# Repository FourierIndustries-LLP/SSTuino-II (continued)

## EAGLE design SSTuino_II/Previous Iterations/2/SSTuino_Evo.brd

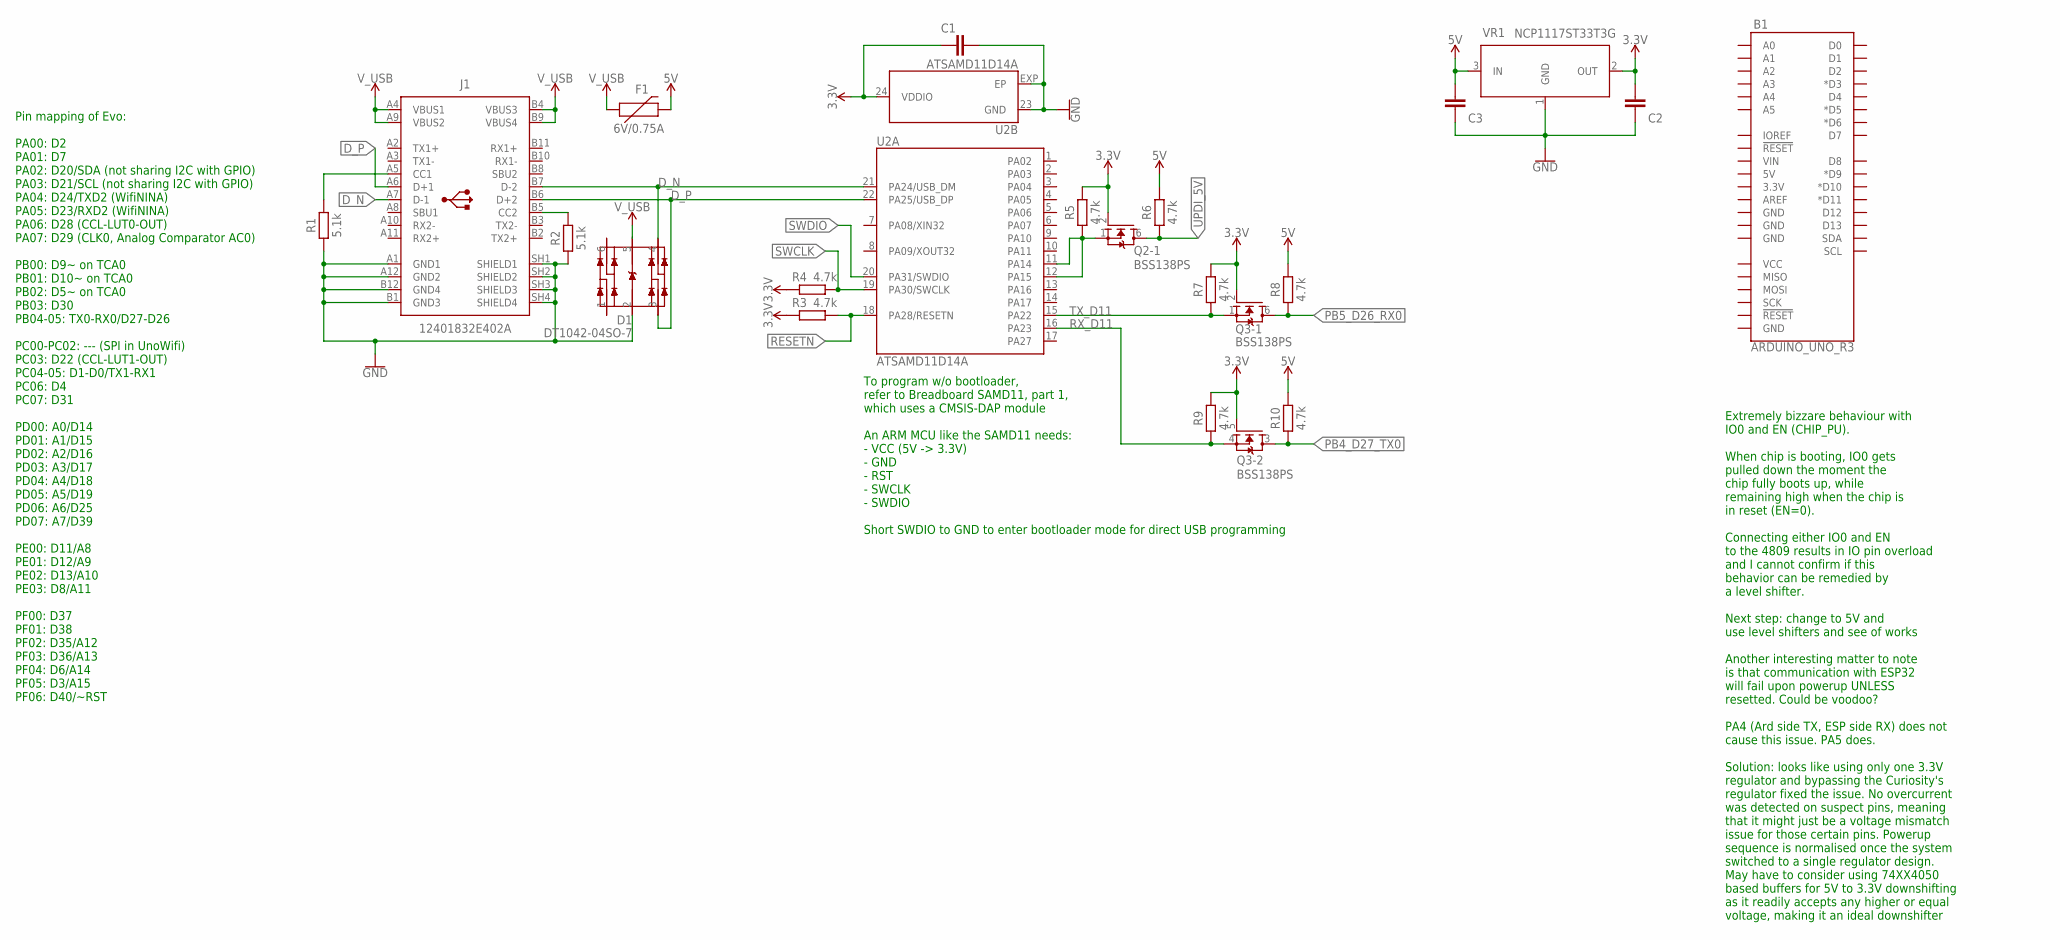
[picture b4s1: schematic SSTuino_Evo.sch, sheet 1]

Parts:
B1: ARDUINO_UNO_R3; ARDUINO_R3
C1: 100n; CAPC1005X60
C2, C3: 10uF; CAPC1608X85
D1: DT1042-04SO-7; SOT95P285X140-6N
F1: 6V/0.75A; 1206
J1: 12401832E402A
Q2, Q3: BSS138PS; ARDUINO-TRANSISTORS_SOT363
R1, R2: 5.1k; RESC1005X40
R3, R4, R5, R6, R7, R8, R9, R10: 4.7k; RESC1005X40
U2: ATSAMD11D14A; ARDUINO-UCS&SOCS_HVQFN24
VR1: NCP1117ST33T3G; SOT230P700X170-4

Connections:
3.3V: C1.1, C2.1, Q2.2 (G), Q3.2 (G), Q3.5 (G), R3.2, R4.2, R5.2, R7.2, R9.2, U2.24 (VDDIO), VR1.2 (OUT); also elsewhere on the board
5V: C3.1, F1.2, R6.2, R8.2, R10.2, VR1.3 (IN); also elsewhere on the board
CC1: J1.A5 (CC1), R1.2
CC2: J1.B5 (CC2), R2.2
D_N: D1.4 (IO3), J1.A7 (D-1), J1.B7 (D-2), U2.21 (PA24/USB_DM)
D_P: D1.3 (IO2), J1.A6 (D+1), J1.B6 (D+2), U2.22 (PA25/USB_DP)
GND: C1.2, C2.2, C3.2, D1.2 (VSS), J1.A1 (GND1), J1.A12 (GND2), J1.B1 (GND3), J1.B12 (GND4), J1.SH1 (SHIELD1), J1.SH2 (SHIELD2), J1.SH3 (SHIELD3), J1.SH4 (SHIELD4), R1.1, R2.1, U2.23 (GND), U2.EXP (EP), VR1.1 (GND); also elsewhere on the board
PB4_D27_TX0: Q3.3 (D), R10.1; also elsewhere on the board
PB5_D26_RX0: Q3.6 (D), R8.1; also elsewhere on the board
RESETN: R3.1, U2.18 (PA28/RESETN)
RX_D11: Q3.4 (S), R9.1, U2.16 (PA23)
SWCLK: R4.1, U2.19 (PA30/SWCLK)
SWDIO: U2.20 (PA31/SWDIO)
TX_D11: Q3.1 (S), R7.1, U2.15 (PA22)
UPDI_3V3: Q2.1 (S), R5.1, U2.11 (PA14), U2.12 (PA15)
UPDI_5V: Q2.6 (D), R6.1
V_USB: D1.5 (VCC), F1.1, J1.A4 (VBUS1), J1.A9 (VBUS2), J1.B4 (VBUS3), J1.B9 (VBUS4)

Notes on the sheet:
Pin mapping of Evo: PA00: D2 PA01: D7 PA02: D20/SDA (not sharing I2C with GPIO) PA03: D21/SCL (not sharing I2C with GPIO) PA04: D24/TXD2 (WifiNINA) PA05: D23/RXD2 (WifiNINA) PA06: D28 (CCL-LUT0-OUT) PA07: D29 (CLK0, Analog Comparator AC0) PB00: D9~ on TCA0 PB01: D10~ on TCA0 PB02: D5~ on TCA0 PB03: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
To program w/o bootloader, refer to Breadboard SAMD11, part 1, which uses a CMSIS-DAP module An ARM MCU like the SAMD11 needs: - VCC (5V -> 3.3V) - GND - RST - SWCLK - SWDIO Short SWDIO to GND to enter bootloader mode for direct USB programming
Extremely bizzare behaviour with IO0 and EN (CHIP_PU). When chip is booting, IO0 gets pulled down the moment the chip fully boots up, while remaining high when the chip is in reset (EN=0). Connecting either IO0 and EN to the 4809 results in IO pin overload and I cannot confirm if this behavior can 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

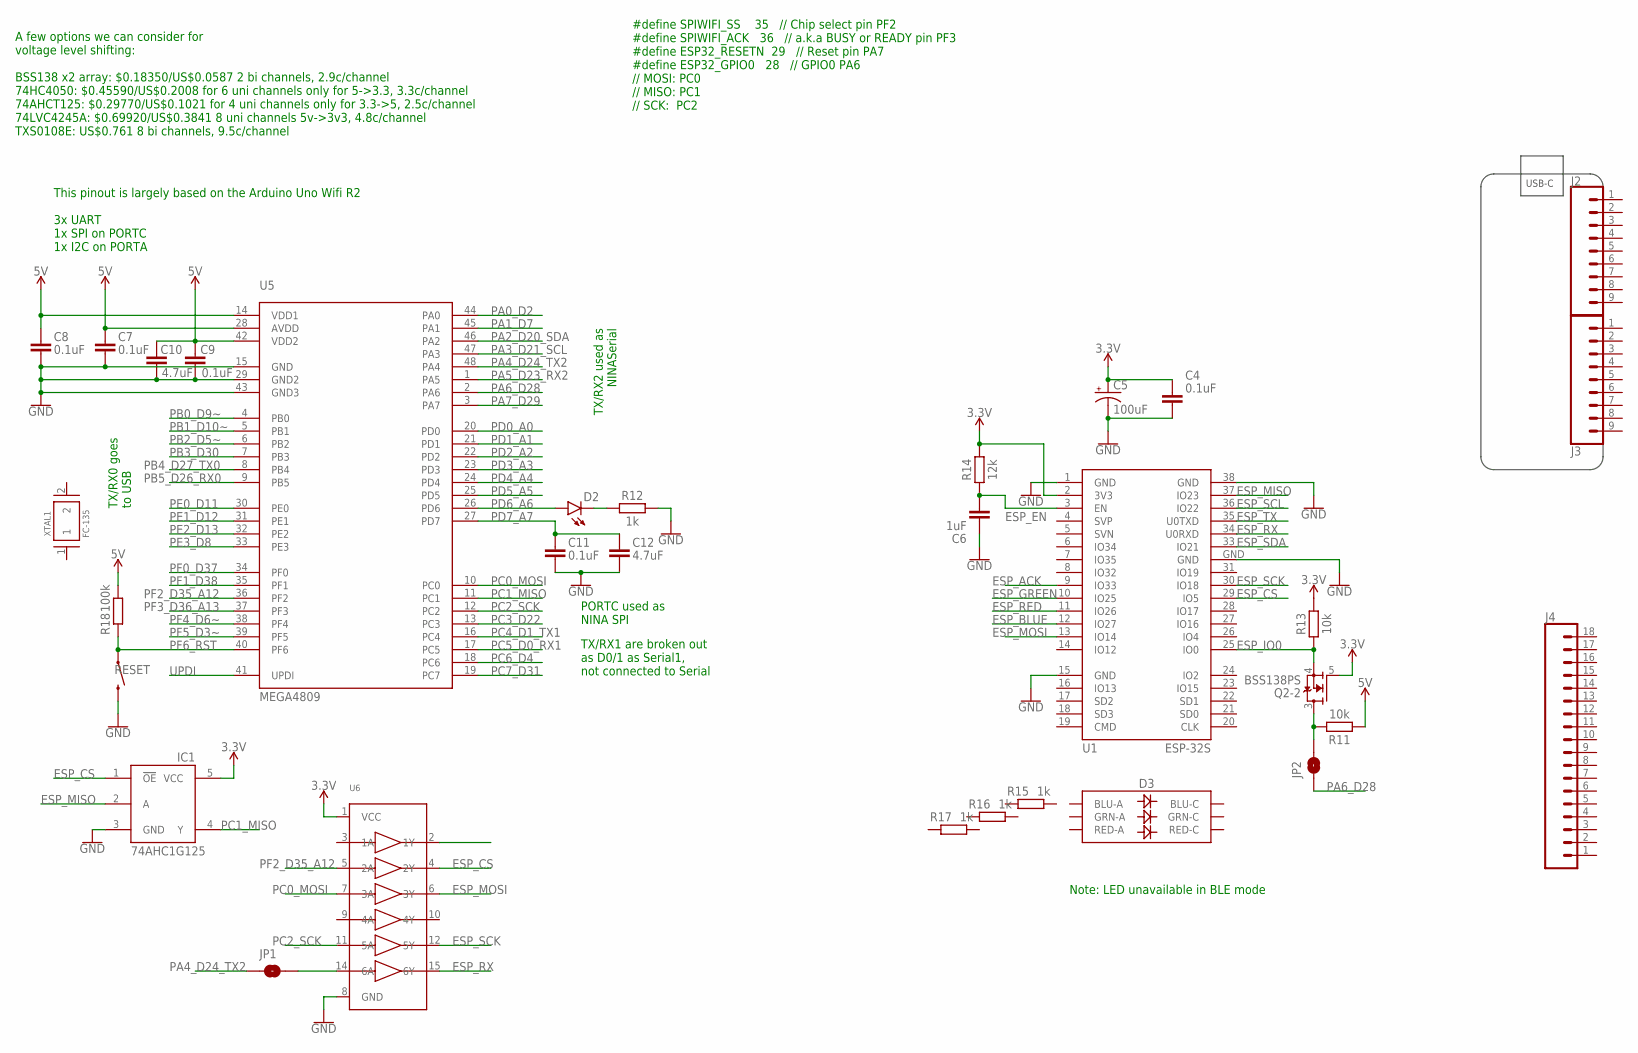
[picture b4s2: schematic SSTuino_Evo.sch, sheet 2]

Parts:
C4, C7, C8, C9, C11: 0.1uF; CAPC1005X60
C5: 100uF; CAPMP3216X180N
C6: 1uF; CAPC1005X60
C10, C12: 4.7uF; CAPC1005X60
D2: LED0603; LED-0603
D3: LED-RGBNO_IC; LED-TRICOLOR-5050
IC1: 74AHC1G125; SOT23-5L
J2, J3: CONN_09NO_SILK; 1X09_NO_SILK
J4: CONN_18; 1X18
JP1, JP2: JUMPER-SMT_2_NO_SILK; SMT-JUMPER_2_NO_SILK
Q2: BSS138PS; ARDUINO-TRANSISTORS_SOT363
R11, R13: 10k; RESC1005X40
R12, R15, R16, R17: 1k; RESC1005X40
R14: 12k; RESC1005X40
R18: 100k; RESC1005X40
RESET: MOMENTARY-SWITCH-SPST-SMD-4.6X2.8MM; TACTILE_SWITCH_SMD_4.6X2.8MM
U1: ESP-32S
U5: MEGA4809; TQFP48
U6: 74HC4050DTSSOP; TSSOP16
XTAL1: FC-135; XTAL330X1051X90N

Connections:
3.3V: C4.1, C5.1 (+), IC1.5 (VCC), Q2.5 (G), R13.2, R14.2, U1.2 (3V3), U6.1 (VCC); also elsewhere on the board
5V: C7.1, C8.1, C9.1, C10.1, R11.1, R18.2, U5.14 (VDD1), U5.28 (AVDD), U5.42 (VDD2); also elsewhere on the board
ESP_ACK: U1.9 (IO33)
ESP_BLUE: U1.12 (IO27)
ESP_CS: IC1.1 (!OE), U1.29 (IO5), U6.4 (2Y)
ESP_EN: C6.2, R14.1, U1.3 (EN)
ESP_GREEN: U1.10 (IO25)
ESP_IO0: Q2.4 (S), R13.1, U1.25 (IO0)
ESP_MISO: IC1.2 (A), U1.37 (IO23)
ESP_MOSI: U1.13 (IO14), U6.6 (3Y)
ESP_RED: U1.11 (IO26)
ESP_RX: U1.34 (U0RXD), U6.15 (6Y)
ESP_SCK: U1.30 (IO18), U6.12 (5Y)
ESP_SCL: U1.36 (IO22)
ESP_SDA: U1.33 (IO21)
ESP_TX: U1.35 (U0TXD)
GND: C4.2, C5.2 (-), C6.1, C7.2, C8.2, C9.2, C10.2, C11.2, C12.2, IC1.3 (GND), R12.2, RESET.3 (2), RESET.4 (2), U1.1 (GND), U1.15 (GND), U1.38 (GND), U1.GND, U5.15 (GND), U5.29 (GND2), U5.43 (GND3), U6.8 (GND); also elsewhere on the board
unnamed: JP2.2, Q2.3 (D), R11.2
unnamed: D2.C, R12.1
unnamed: JP1.2, U6.14 (6A)
PA0_D2: U5.44 (PA0)
PA1_D7: U5.45 (PA1)
PA2_D20_SDA: U5.46 (PA2)
PA3_D21_SCL: U5.47 (PA3)
PA4_D24_TX2: JP1.1, U5.48 (PA4)
PA5_D23_RX2: U5.1 (PA5)
PA6_D28: JP2.1, U5.2 (PA6)
PA7_D29: U5.3 (PA7)
PB0_D9~: U5.4 (PB0)
PB1_D10~: U5.5 (PB1)
PB2_D5~: U5.6 (PB2)
PB3_D30: U5.7 (PB3)
PB4_D27_TX0: U5.8 (PB4); also elsewhere on the board
PB5_D26_RX0: U5.9 (PB5); also elsewhere on the board
PC0_MOSI: U5.10 (PC0), U6.7 (3A)
PC1_MISO: IC1.4 (Y), U5.11 (PC1)
PC2_SCK: U5.12 (PC2), U6.11 (5A)
PC3_D22: U5.13 (PC3)
PC4_D1_TX1: U5.16 (PC4)
PC5_D0_RX1: U5.17 (PC5)
PC6_D4: U5.18 (PC6)
PC7_D31: U5.19 (PC7)
PD0_A0: U5.20 (PD0)
PD1_A1: U5.21 (PD1)
PD2_A2: U5.22 (PD2)
PD3_A3: U5.23 (PD3)
PD4_A4: U5.24 (PD4)
PD5_A5: U5.25 (PD5)
PD6_A6: D2.A, U5.26 (PD6)
PD7_A7: C11.1, C12.1, U5.27 (PD7)
PE0_D11: U5.30 (PE0)
PE1_D12: U5.31 (PE1)
PE2_D13: U5.32 (PE2)
PE3_D8: U5.33 (PE3)
PF0_D37: U5.34 (PF0)
PF1_D38: U5.35 (PF1)
PF2_D35_A12: U5.36 (PF2), U6.5 (2A)
PF3_D36_A13: U5.37 (PF3)
PF4_D6~: U5.38 (PF4)
PF5_D3~: U5.39 (PF5)
PF6_RST: R18.1, RESET.1, RESET.2 (1), U5.40 (PF6)
UPDI: U5.41 (UPDI)

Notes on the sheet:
A few options we can consider for voltage level shifting: BSS138 x2 array: $0.18350/US$0.0587 2 bi channels, 2.9c/channel 74HC4050: $0.45590/US$0.2008 for 6 uni channels only for 5->3.3, 3.3c/channel 74AHCT125: $0.29770/US$0.1021 for 4 uni channels only for 3.3->5, 2.5c/channel 74LVC4245A: $0.69920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
This pinout is largely based on the Arduino Uno Wifi R2 3x UART 1x SPI on PORTC 1x I2C on PORTA
TX/RX2 used as NINASerial
PORTC used as NINA SPI
TX/RX1 are broken out as D0/1 as Serial1, not connected to Serial
TX/RX0 goes to USB
#define SPIWIFI_SS 35 // Chip select pin PF2 #define SPIWIFI_ACK 36 // a.k.a BUSY or READY pin PF3 #define ESP32_RESETN 29 // Reset pin PA7 #define ESP32_GPIO0 28 // GPIO0 PA6 // MOSI: PC0 // MISO: PC1 // SCK: PC2
Note: LED unavailable in BLE mode
USB-C

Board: 2 copper layers, 51 parts (0 on the bottom side), 35 nets, no tracks yet.

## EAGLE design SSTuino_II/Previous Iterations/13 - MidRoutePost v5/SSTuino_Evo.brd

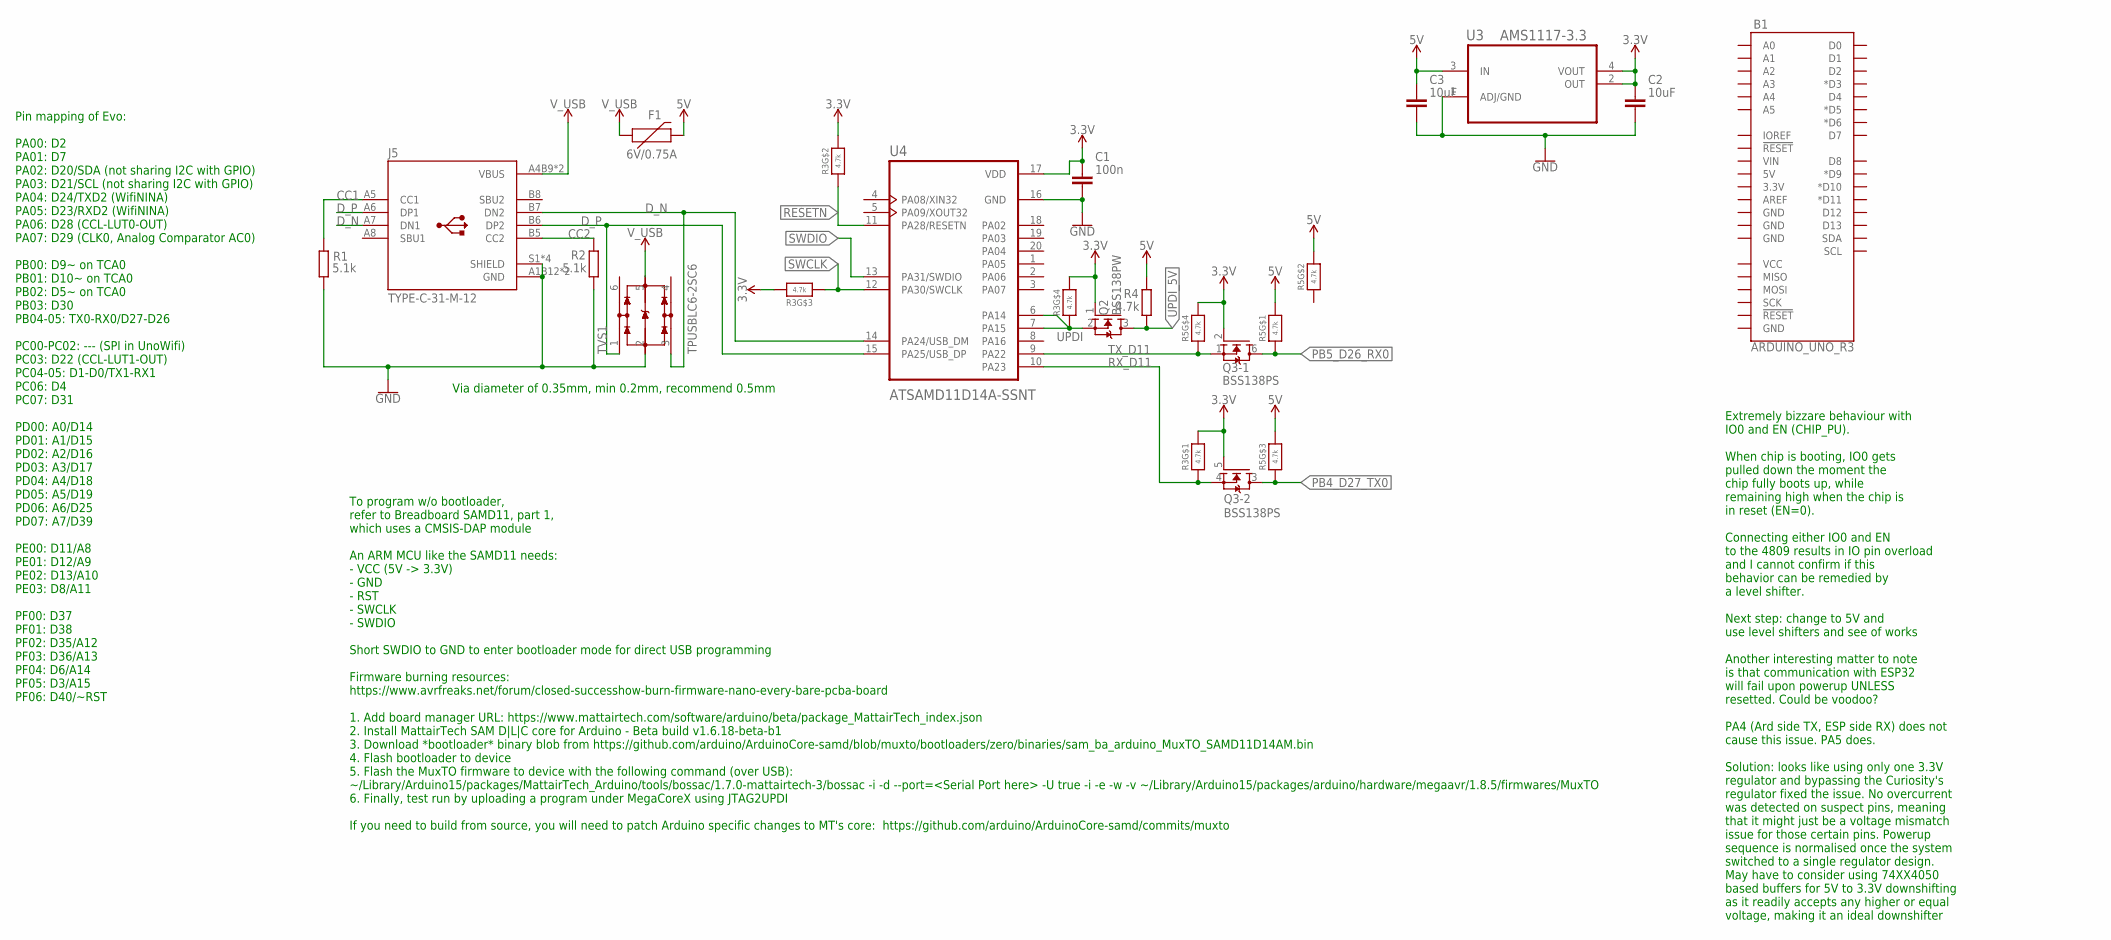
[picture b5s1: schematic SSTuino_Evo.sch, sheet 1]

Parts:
B1: ARDUINO_UNO_R3; ARDUINO_R3
C1: 100n; CAPC1005X60
C2, C3: 10uF; CAPC1608X85
F1: 6V/0.75A; 1206; LCSC_PART C99563
J5: TYPE-C-31-M-12; HRO_TYPE-C-31-M-12; LCSC_PART C165948
Q2: BSS138PW; SOT65P210X110-3N
Q3: BSS138PS; ARDUINO-TRANSISTORS_SOT363; LCSC_PART C193381
R1, R2: 5.1k; RESC1005X40
R3, R5: 4.7k; RESPACK_4X0402; LCSC_PART C1980
R4: 4.7k; RESC1005X40
TVS1: TPUSBLC6-2SC6; SOT95P280X110-6N; LCSC_PART C558442
U3: AMS1117-3.3; SOT230P696X180-4N; LCSC_PART C6186
U4: ATSAMD11D14A-SSNT; SOIC127P1030X265-20N; LCSC_PART C2053599

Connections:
3.3V: C1.1, C2.1, Q2.1 (G), Q3.2 (G), Q3.5 (G), R3.5 (2), R3.6 (2), R3.7 (2), R3.8 (2), R5.5 (2), U3.2 (OUT), U3.4 (VOUT), U4.17 (VDD); also elsewhere on the board
5V: C3.1, F1.2, R4.2, R5.6 (2), R5.7 (2), R5.8 (2), U3.3 (IN); also elsewhere on the board
CC1: J5.A5 (CC1), R1.1
CC2: J5.B5 (CC2), R2.2
D_N: J5.A7 (DN1), J5.B7 (DN2), TVS1.3 (IO2), U4.14 (PA24/USB_DM)
D_P: J5.A6 (DP1), J5.B6 (DP2), TVS1.1 (IO1), U4.15 (PA25/USB_DP)
GND: C1.2, C2.2, C3.2, J5.A1B12 (GND), J5.B1A12 (GND), J5.S1 (SHIELD), J5.S2 (SHIELD), J5.S3 (SHIELD), J5.S4 (SHIELD), R1.2, R2.1, TVS1.2 (VSS), U3.1 (ADJ/GND), U4.16 (GND); also elsewhere on the board
PB4_D27_TX0: Q3.3 (D), R5.3 (1); also elsewhere on the board
PB5_D26_RX0: Q3.6 (D), R5.1; also elsewhere on the board
RESETN: R3.2 (1), U4.11 (PA28/RESETN); also elsewhere on the board
RX_D11: Q3.4 (S), R3.1, U4.10 (PA23)
SWCLK: R3.3 (1), U4.12 (PA30/SWCLK); also elsewhere on the board
SWDIO: U4.13 (PA31/SWDIO); also elsewhere on the board
TX_D11: Q3.1 (S), R5.4 (1), U4.9 (PA22)
UPDI: Q2.2 (S), R3.4 (1), U4.6 (PA14), U4.7 (PA15)
UPDI_5V: Q2.3 (D), R4.1; also elsewhere on the board
V_USB: F1.1, J5.A4B9 (VBUS), J5.B4A9 (VBUS), TVS1.5 (VCC)

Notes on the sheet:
Pin mapping of Evo: PA00: D2 PA01: D7 PA02: D20/SDA (not sharing I2C with GPIO) PA03: D21/SCL (not sharing I2C with GPIO) PA04: D24/TXD2 (WifiNINA) PA05: D23/RXD2 (WifiNINA) PA06: D28 (CCL-LUT0-OUT) PA07: D29 (CLK0, Analog Comparator AC0) PB00: D9~ on TCA0 PB01: D10~ on TCA0 PB02: D5~ on TCA0 PB03: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
To program w/o bootloader, refer to Breadboard SAMD11, part 1, which uses a CMSIS-DAP module An ARM MCU like the SAMD11 needs: - VCC (5V -> 3.3V) - GND - RST - SWCLK - SWDIO Short SWDIO to GND to enter bootloader mode for direct USB programming Firmware burning resources: https://www.avrfreaks.net/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
Extremely bizzare behaviour with IO0 and EN (CHIP_PU). When chip is booting, IO0 gets pulled down the moment the chip fully boots up, while remaining high when the chip is in reset (EN=0). Connecting either IO0 and EN to the 4809 results in IO pin overload and I cannot confirm if this behavior can 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
Via diameter of 0.35mm, min 0.2mm, recommend 0.5mm

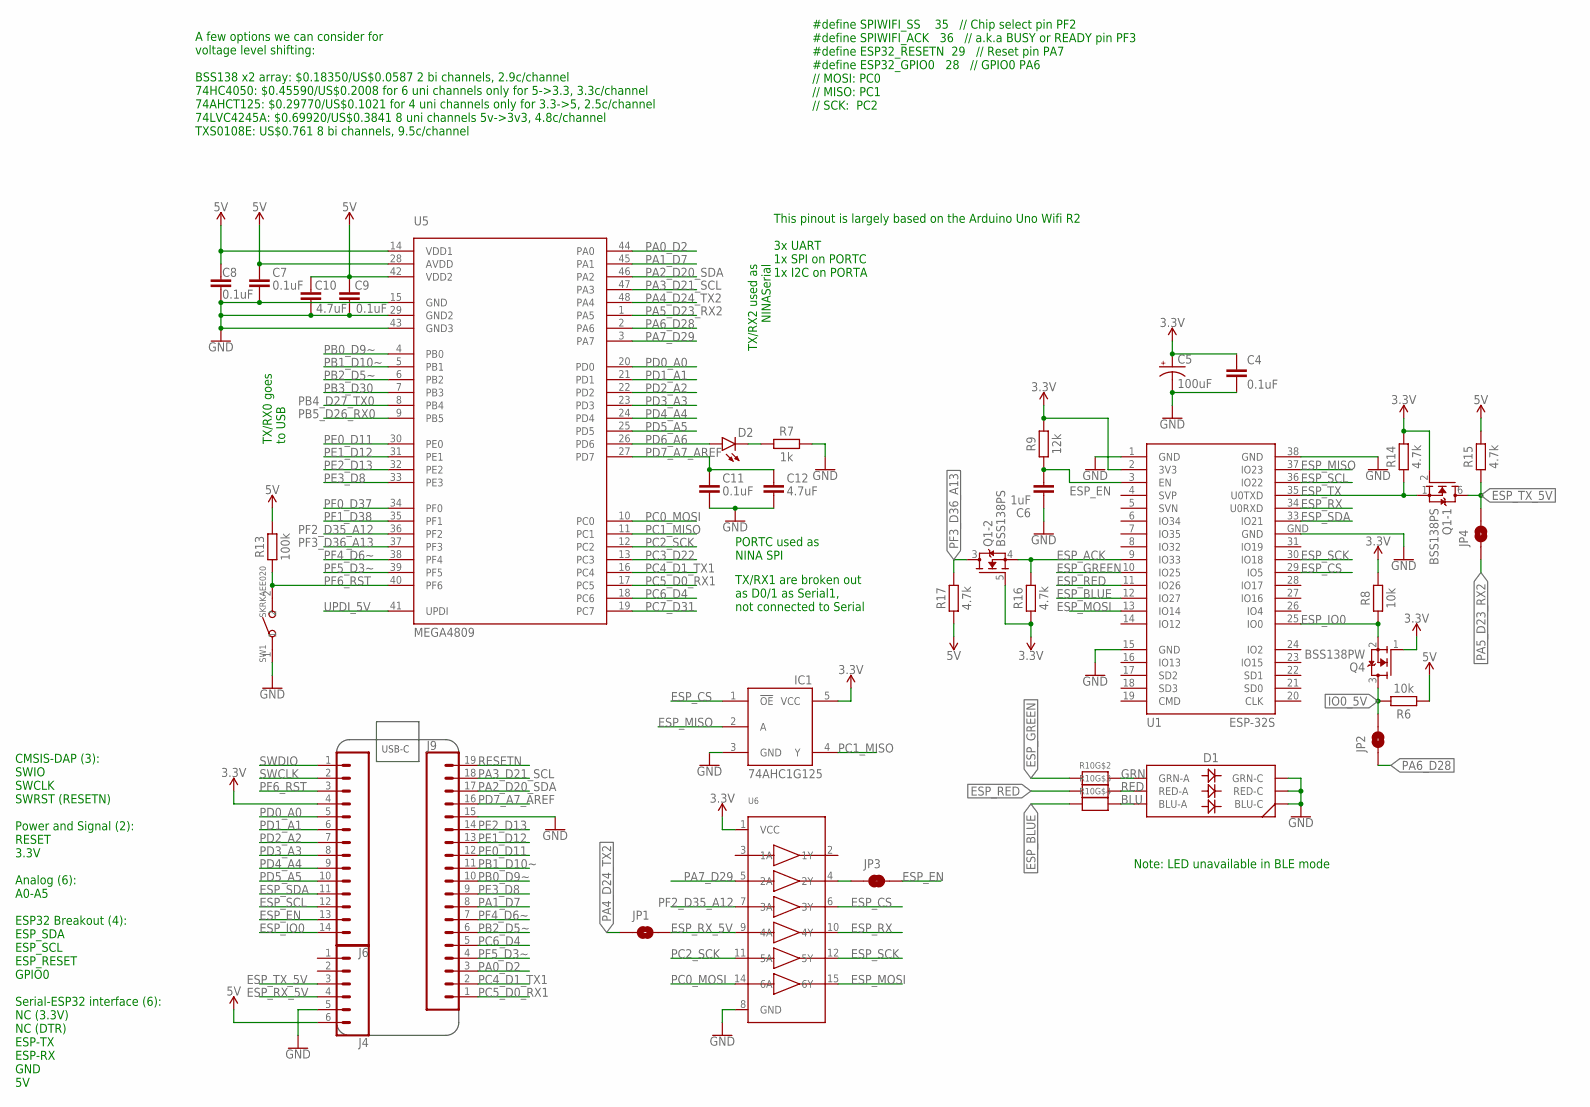
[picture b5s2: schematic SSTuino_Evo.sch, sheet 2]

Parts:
C4, C7, C8, C9, C11: 0.1uF; CAPC1005X60
C5: 100uF; CAPMP3216X180N
C6: 1uF; CAPC1005X60
C10, C12: 4.7uF; CAPC1005X60
D1: LED-RGBTC5050RGBF08; LED-TRICOLOR-5050
D2: LED0603; LED-0603
IC1: 74AHC1G125; SOT23-5L; LCSC_PART C124295
J4: CONN_06NO_SILK_FEMALE_PTH; 1X06_NO_SILK
J6: CONN_14NO_SILK; 1X14_NO_SILK
J9: CONN_191X19_NO_SILK; 1X19_NO_SILK
JP1, JP2, JP4: JUMPER-SMT_2_NO_SILK; SMT-JUMPER_2_NO_SILK
JP3: JUMPER-SMT_2_NC_TRACE_SILK; SMT-JUMPER_2_NC_TRACE_SILK
Q1: BSS138PS; ARDUINO-TRANSISTORS_SOT363; LCSC_PART C193381
Q4: BSS138PW; SOT65P210X110-3N
R6, R8: 10k; RESC1005X40
R7: 1k; RESC1005X40
R9: 12k; RESC1005X40
R10: RESISTOR_4PACK0402; RESPACK_4X0402
R13: 100k; RESC1005X40
R14, R15, R16, R17: 4.7k; RESC1005X40
SW1: SKRKAEE020; SW2-2.6-3.9X2.9X1.5+0.4MM; LCSC_PART C115357
U1: ESP-32S
U5: MEGA4809; TQFP48; LCSC_PART C189475
U6: 74HC4050DTSSOP; TSSOP16; LCSC_PART C352825

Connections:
3.3V: C4.1, C5.1 (+), IC1.5 (VCC), J6.4, Q1.2 (G), Q1.5 (G), Q4.1 (G), R8.2, R9.2, R14.2, R16.1, U1.2 (3V3), U6.1 (VCC); also elsewhere on the board
5V: C7.1, C8.1, C9.1, C10.1, J4.6, R6.1, R13.2, R15.2, R17.1, U5.14 (VDD1), U5.28 (AVDD), U5.42 (VDD2); also elsewhere on the board
BLU: D1.6 (BLU-A), R10.5 (2)
ESP_ACK: Q1.4 (S), R16.2, U1.9 (IO33)
ESP_BLUE: R10.4 (1), U1.12 (IO27)
ESP_CS: IC1.1 (!OE), U1.29 (IO5), U6.6 (3Y)
ESP_EN: C6.2, J6.13, JP3.2, R9.1, U1.3 (EN)
ESP_GREEN: R10.2 (1), U1.10 (IO25)
ESP_IO0: J6.14, Q4.2 (S), R8.1, U1.25 (IO0)
ESP_MISO: IC1.2 (A), U1.37 (IO23)
ESP_MOSI: U1.13 (IO14), U6.15 (6Y)
ESP_RED: R10.3 (1), U1.11 (IO26)
ESP_RX: U1.34 (U0RXD), U6.10 (4Y)
ESP_RX_5V: J4.4, JP1.2, U6.9 (4A)
ESP_SCK: U1.30 (IO18), U6.12 (5Y)
ESP_SCL: J6.12, U1.36 (IO22)
ESP_SDA: J6.11, U1.33 (IO21)
ESP_TX: Q1.1 (S), R14.1, U1.35 (U0TXD)
ESP_TX_5V: J4.3, JP4.2, Q1.6 (D), R15.1
GND: C4.2, C5.2 (-), C6.1, C7.2, C8.2, C9.2, C10.2, C11.2, C12.2, D1.1 (BLU-C), D1.2 (RED-C), D1.3 (GRN-C), IC1.3 (GND), J4.5, J9.15, R7.2, SW1.1, U1.1 (GND), U1.15 (GND), U1.38 (GND), U1.GND, U5.15 (GND), U5.29 (GND2), U5.43 (GND3), U6.8 (GND); also elsewhere on the board
GRN: D1.4 (GRN-A), R10.7 (2)
IO0_5V: JP2.2, Q4.3 (D), R6.2
unnamed: D2.C, R7.1
unnamed: JP3.1, U6.4 (2Y)
PA0_D2: J9.3, U5.44 (PA0)
PA1_D7: J9.8, U5.45 (PA1)
PA2_D20_SDA: J9.17, U5.46 (PA2)
PA3_D21_SCL: J9.18, U5.47 (PA3)
PA4_D24_TX2: JP1.1, U5.48 (PA4)
PA5_D23_RX2: JP4.1, U5.1 (PA5)
PA6_D28: JP2.1, U5.2 (PA6)
PA7_D29: U5.3 (PA7), U6.5 (2A)
PB0_D9~: J9.10, U5.4 (PB0)
PB1_D10~: J9.11, U5.5 (PB1)
PB2_D5~: J9.6, U5.6 (PB2)
PB3_D30: U5.7 (PB3)
PB4_D27_TX0: U5.8 (PB4); also elsewhere on the board
PB5_D26_RX0: U5.9 (PB5); also elsewhere on the board
PC0_MOSI: U5.10 (PC0), U6.14 (6A)
PC1_MISO: IC1.4 (Y), U5.11 (PC1)
PC2_SCK: U5.12 (PC2), U6.11 (5A)
PC3_D22: U5.13 (PC3)
PC4_D1_TX1: J9.2, U5.16 (PC4)
PC5_D0_RX1: J9.1, U5.17 (PC5)
PC6_D4: J9.5, U5.18 (PC6)
PC7_D31: U5.19 (PC7)
PD0_A0: J6.5, U5.20 (PD0)
PD1_A1: J6.6, U5.21 (PD1)
PD2_A2: J6.7, U5.22 (PD2)
PD3_A3: J6.8, U5.23 (PD3)
PD4_A4: J6.9, U5.24 (PD4)
PD5_A5: J6.10, U5.25 (PD5)
PD6_A6: D2.A, U5.26 (PD6)
PD7_A7_AREF: C11.1, C12.1, J9.16, U5.27 (PD7)
PE0_D11: J9.12, U5.30 (PE0)
PE1_D12: J9.13, U5.31 (PE1)
PE2_D13: J9.14, U5.32 (PE2)
PE3_D8: J9.9, U5.33 (PE3)
PF0_D37: U5.34 (PF0)
PF1_D38: U5.35 (PF1)
PF2_D35_A12: U5.36 (PF2), U6.7 (3A)
PF3_D36_A13: Q1.3 (D), R17.2, U5.37 (PF3)
PF4_D6~: J9.7, U5.38 (PF4)
PF5_D3~: J9.4, U5.39 (PF5)
PF6_RST: J6.3, R13.1, SW1.2, U5.40 (PF6)
RED: D1.5 (RED-A), R10.6 (2)
RESETN: J9.19; also elsewhere on the board
SWCLK: J6.2; also elsewhere on the board
SWDIO: J6.1; also elsewhere on the board
UPDI_5V: U5.41 (UPDI); also elsewhere on the board

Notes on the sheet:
A few options we can consider for voltage level shifting: BSS138 x2 array: $0.18350/US$0.0587 2 bi channels, 2.9c/channel 74HC4050: $0.45590/US$0.2008 for 6 uni channels only for 5->3.3, 3.3c/channel 74AHCT125: $0.29770/US$0.1021 for 4 uni channels only for 3.3->5, 2.5c/channel 74LVC4245A: $0.69920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
This pinout is largely based on the Arduino Uno Wifi R2 3x UART 1x SPI on PORTC 1x I2C on PORTA
TX/RX2 used as NINASerial
PORTC used as NINA SPI
TX/RX1 are broken out as D0/1 as Serial1, not connected to Serial
TX/RX0 goes to USB
#define SPIWIFI_SS 35 // Chip select pin PF2 #define SPIWIFI_ACK 36 // a.k.a BUSY or READY pin PF3 #define ESP32_RESETN 29 // Reset pin PA7 #define ESP32_GPIO0 28 // GPIO0 PA6 // MOSI: PC0 // MISO: PC1 // SCK: PC2
Note: LED unavailable in BLE mode
USB-C
CMSIS-DAP (3): SWIO SWCLK SWRST (RESETN) Power and Signal (2): RESET 3.3V Analog (6): A0-A5 ESP32 Breakout (4): ESP_SDA ESP_SCL ESP_RESET GPIO0 Serial-ESP32 interface (6): NC (3.3V) NC (DTR) ESP-TX ESP-RX GND 5V

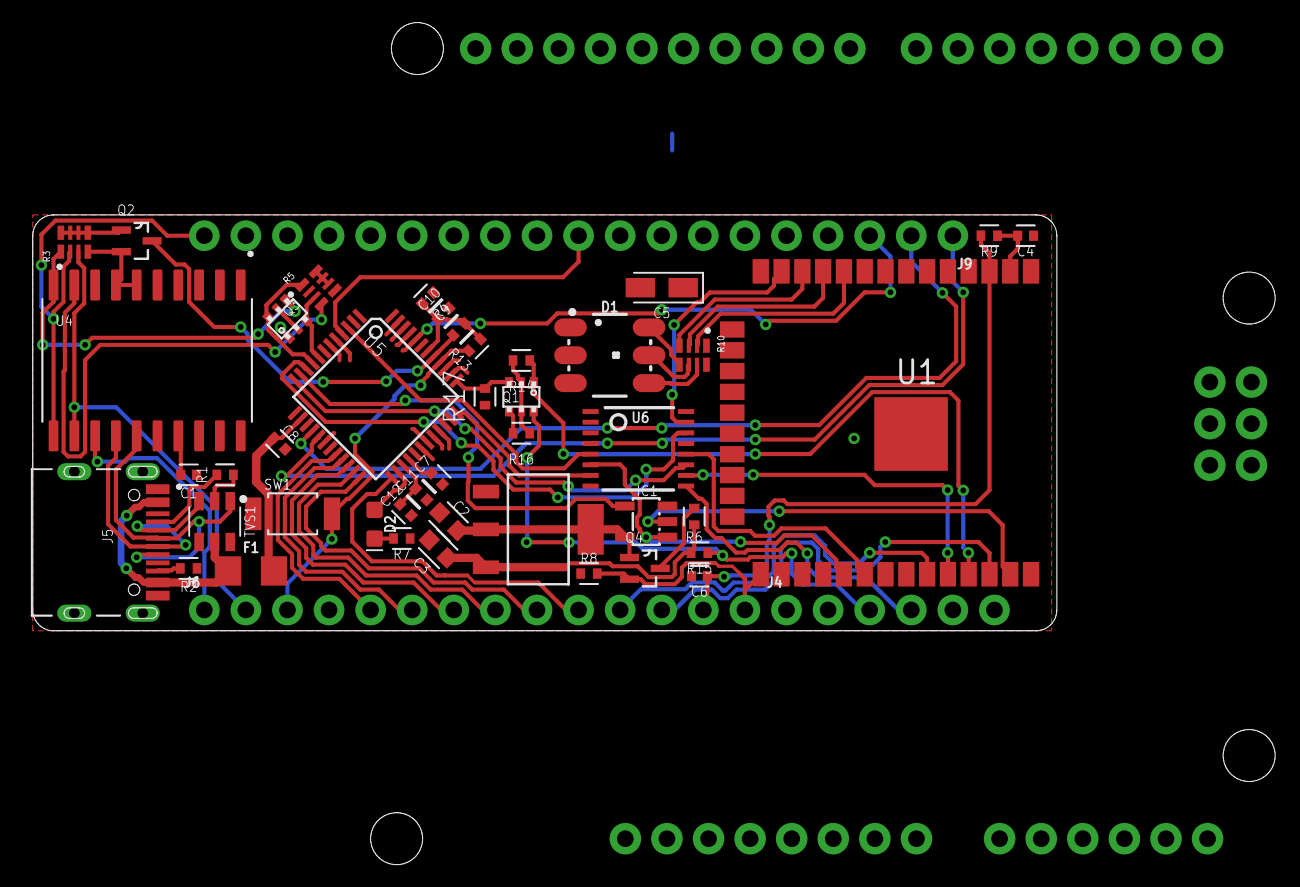
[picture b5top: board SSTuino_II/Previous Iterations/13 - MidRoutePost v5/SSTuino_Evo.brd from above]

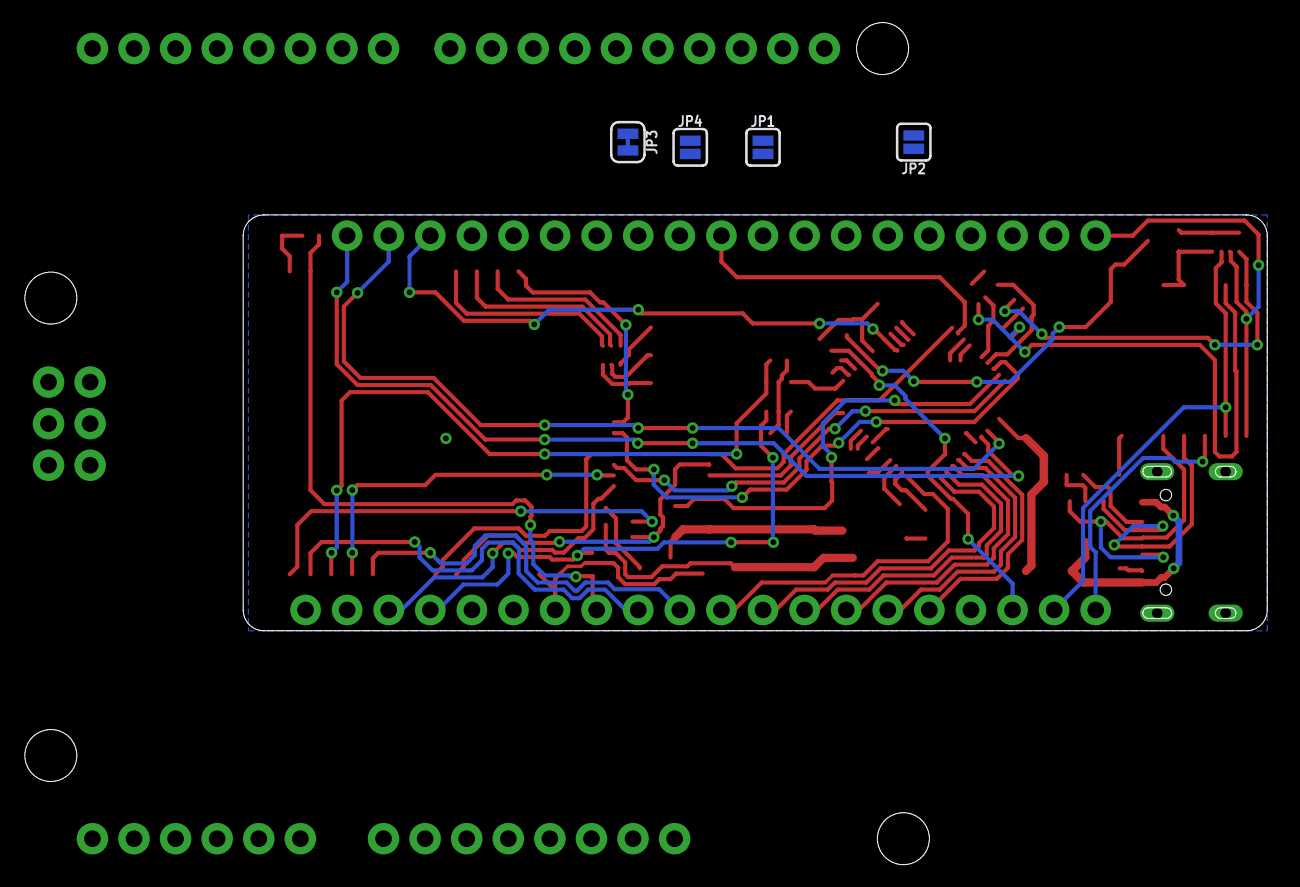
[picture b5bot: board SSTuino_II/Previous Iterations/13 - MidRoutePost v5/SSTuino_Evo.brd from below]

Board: 2 copper layers, 62.5 x 25.4 mm, 51 parts (4 on the bottom side), 73 nets.

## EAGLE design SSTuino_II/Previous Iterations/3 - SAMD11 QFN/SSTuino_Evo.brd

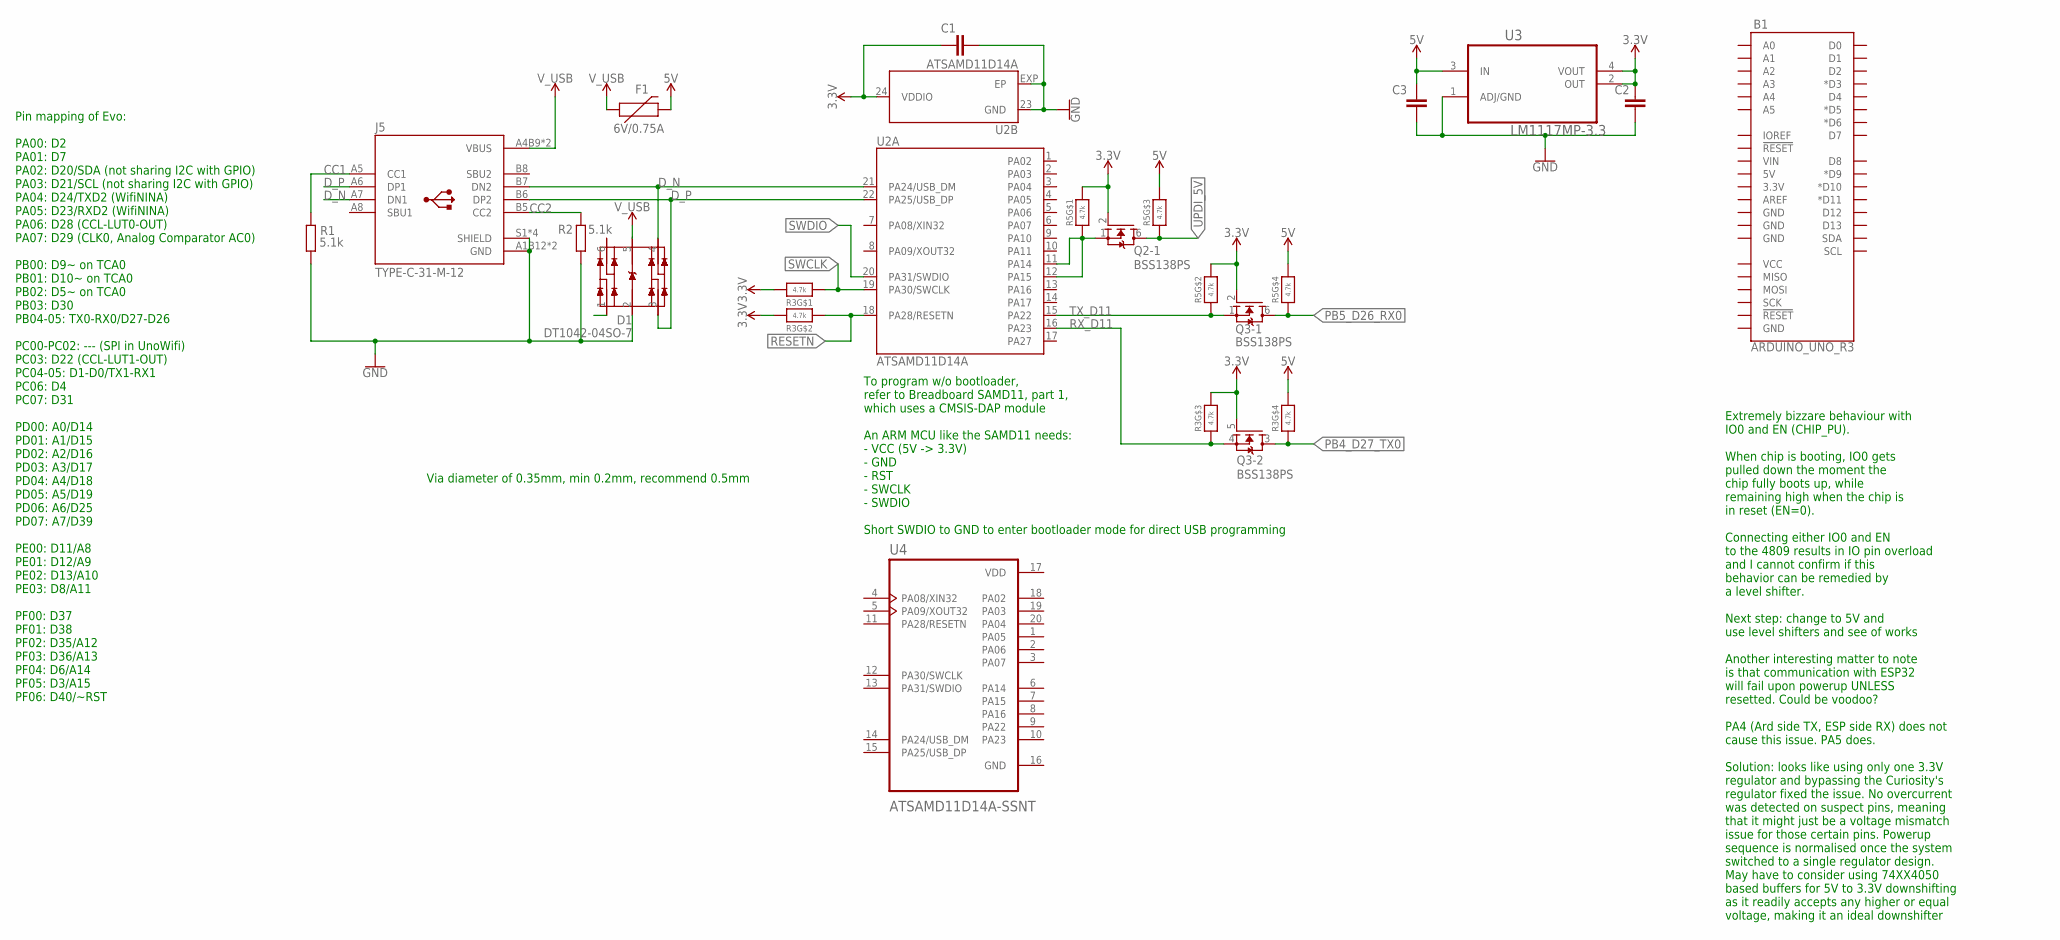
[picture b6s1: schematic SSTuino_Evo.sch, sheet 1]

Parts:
B1: ARDUINO_UNO_R3; ARDUINO_R3
C1: 100n; CAPC1005X60
C2, C3: 10uF; CAPC1608X85
D1: DT1042-04SO-7; SOT95P285X140-6N
F1: 6V/0.75A; 1206
J5: TYPE-C-31-M-12; HRO_TYPE-C-31-M-12
Q2, Q3: BSS138PS; ARDUINO-TRANSISTORS_SOT363; LCSC_PART C193381
R1, R2: 5.1k; RESC1005X40
R3, R5: 4.7k; RESPACK_4X0402
U2: ATSAMD11D14A; ARDUINO-UCS&SOCS_HVQFN24
U3: LM1117MP-3.3; SOT230P696X180-4N
U4: ATSAMD11D14A-SSNT; SOIC127P1030X265-20N

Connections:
3.3V: C1.1, C2.1, Q2.2 (G), Q3.2 (G), Q3.5 (G), R3.6 (2), R3.7 (2), R3.8 (2), R5.7 (2), R5.8 (2), U2.24 (VDDIO), U3.2 (OUT), U3.4 (VOUT); also elsewhere on the board
5V: C3.1, F1.2, R3.5 (2), R5.5 (2), R5.6 (2), U3.3 (IN); also elsewhere on the board
CC1: J5.A5 (CC1), R1.1
CC2: J5.B5 (CC2), R2.2
D_N: D1.4 (IO3), J5.A7 (DN1), J5.B7 (DN2), U2.21 (PA24/USB_DM)
D_P: D1.3 (IO2), J5.A6 (DP1), J5.B6 (DP2), U2.22 (PA25/USB_DP)
GND: C1.2, C2.2, C3.2, D1.2 (VSS), J5.A1B12 (GND), J5.B1A12 (GND), J5.S1 (SHIELD), J5.S2 (SHIELD), J5.S3 (SHIELD), J5.S4 (SHIELD), R1.2, R2.1, U2.23 (GND), U2.EXP (EP), U3.1 (ADJ/GND), U4.16 (GND); also elsewhere on the board
PB4_D27_TX0: Q3.3 (D), R3.4 (1); also elsewhere on the board
PB5_D26_RX0: Q3.6 (D), R5.4 (1); also elsewhere on the board
RESETN: R3.2 (1), U2.18 (PA28/RESETN)
RX_D11: Q3.4 (S), R3.3 (1), U2.16 (PA23)
SWCLK: R3.1, U2.19 (PA30/SWCLK); also elsewhere on the board
SWDIO: U2.20 (PA31/SWDIO); also elsewhere on the board
TX_D11: Q3.1 (S), R5.2 (1), U2.15 (PA22)
UPDI_3V3: Q2.1 (S), R5.1, U2.11 (PA14), U2.12 (PA15)
UPDI_5V: Q2.6 (D), R5.3 (1)
VDD: U4.17 (VDD)
V_USB: D1.5 (VCC), F1.1, J5.A4B9 (VBUS), J5.B4A9 (VBUS)

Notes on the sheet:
Pin mapping of Evo: PA00: D2 PA01: D7 PA02: D20/SDA (not sharing I2C with GPIO) PA03: D21/SCL (not sharing I2C with GPIO) PA04: D24/TXD2 (WifiNINA) PA05: D23/RXD2 (WifiNINA) PA06: D28 (CCL-LUT0-OUT) PA07: D29 (CLK0, Analog Comparator AC0) PB00: D9~ on TCA0 PB01: D10~ on TCA0 PB02: D5~ on TCA0 PB03: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
To program w/o bootloader, refer to Breadboard SAMD11, part 1, which uses a CMSIS-DAP module An ARM MCU like the SAMD11 needs: - VCC (5V -> 3.3V) - GND - RST - SWCLK - SWDIO Short SWDIO to GND to enter bootloader mode for direct USB programming
Extremely bizzare behaviour with IO0 and EN (CHIP_PU). When chip is booting, IO0 gets pulled down the moment the chip fully boots up, while remaining high when the chip is in reset (EN=0). Connecting either IO0 and EN to the 4809 results in IO pin overload and I cannot confirm if this behavior can 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
Via diameter of 0.35mm, min 0.2mm, recommend 0.5mm
